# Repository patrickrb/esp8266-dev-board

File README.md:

# esp8266-dev-board
esp8266 dev board

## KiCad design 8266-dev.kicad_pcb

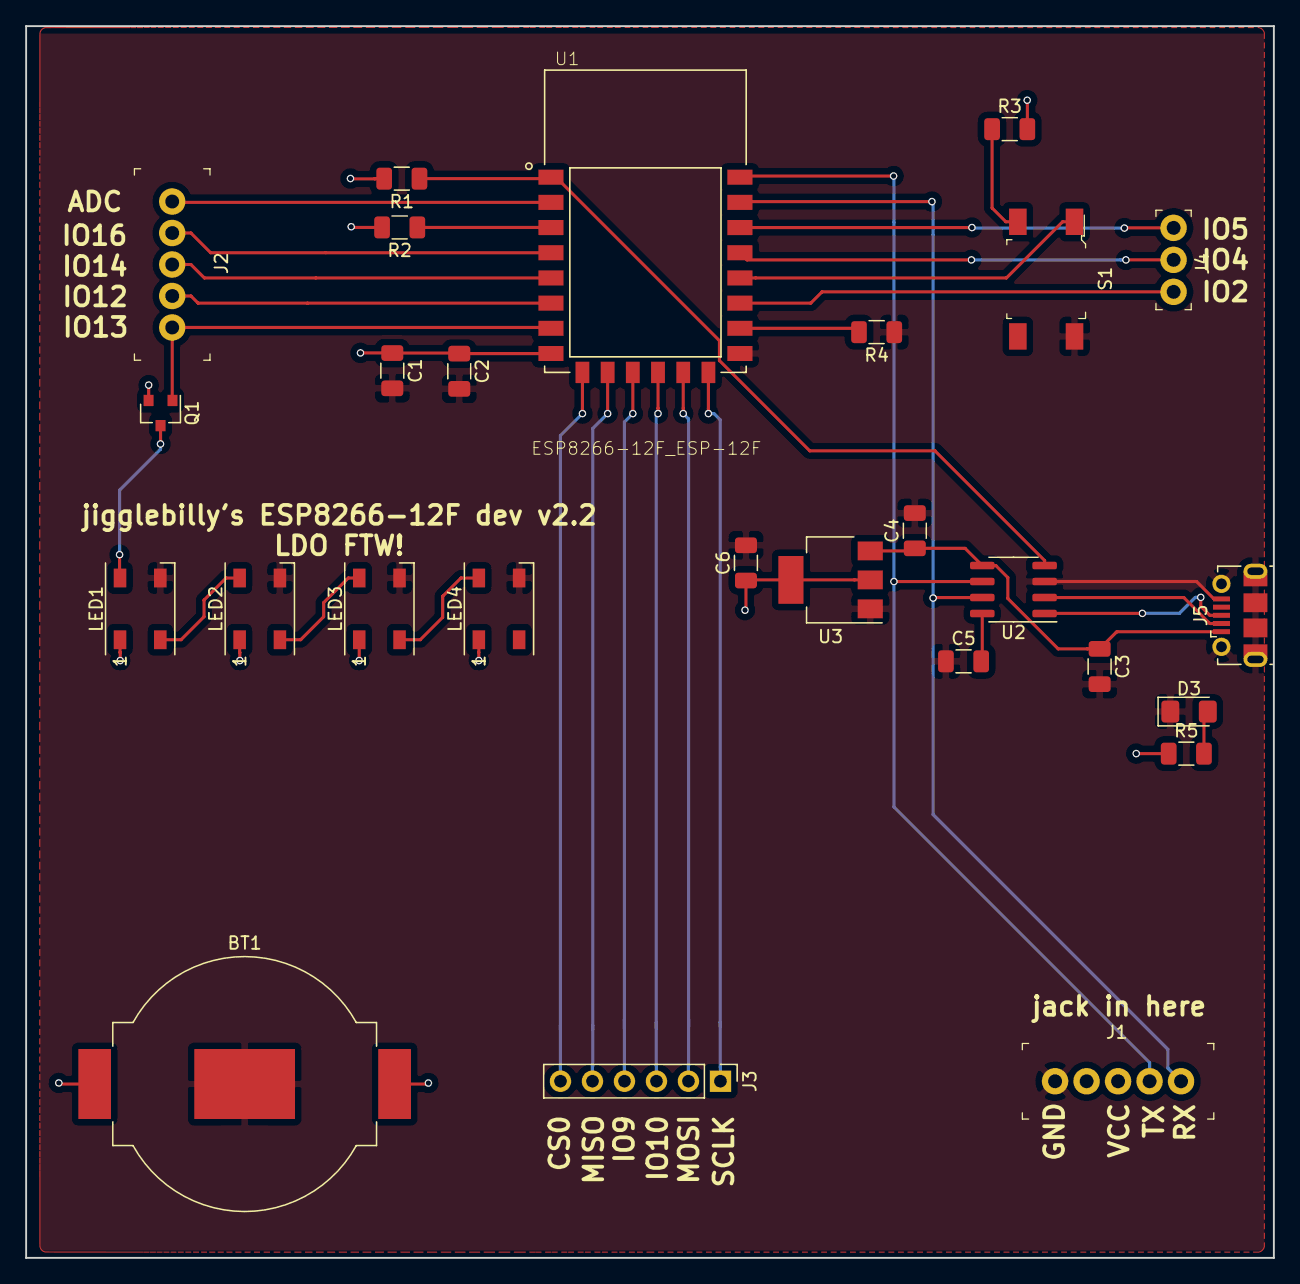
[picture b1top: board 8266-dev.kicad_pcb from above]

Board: 2 copper layers, 99.1 x 97.8 mm, 27 parts (0 on the bottom side), 32 nets.

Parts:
BT1: Battery; BatteryHolder_MPD_BC2003_1x2032
C1: 10uF; C_1206_3216Metric
C2, C3, C5: 100nF; C_1206_3216Metric
C4, C6: 1uF; C_1206_3216Metric
D3: GREEN LED; LED_1206_3216Metric_Pad1.42x1.75mm_HandSolder
J1: Programming headers; PinHeader_1x5_P2.5mm_Drill1.1mm
J2: Left breakout; PinHeader_1x5_P2.5mm_Drill1.1mm
J3: Bottom breakout; PinHeader_1x06_P2.54mm_Vertical
J4: Right breakout; PinHeader_1x3_P2.54_Drill1.1mm
J5: USB_B_Micro; USB_Micro-B_Molex-105017-0001
LED1, LED2, LED3, LED4: WS2812B; LED_WS2812B_PLCC4_5.0x5.0mm_P3.2mm
Q1: BSS138; SOT-23
R1, R2, R3, R4: 10K; R_1206_3216Metric
R5: R; R_1206_3216Metric
S1: 430152070826; Switch_Tactile_SMD_6x6mm
U1: ESP8266-12F_ESP-12F; XCVR_ESP8266-12E%2fESP-12E
U2: CH330N; SOIC-8_3.9x4.9mm_P1.27mm
U3: TLV1117-33; SOT-223-3_TabPin2

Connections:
/ADC: J2.1, U1.2
/CS0: J3.6, U1.9
/D+: J5.3, U2.1
/D-: J5.2, U2.2
/IO2: J4.3, U1.17
/IO4: J4.2, U1.19
/IO5: J4.1, U1.20
/IO9: J3.4, U1.11
/IO10: J3.3, U1.12
/IO12: J2.4, U1.6
/IO13: J2.5, Q1.1, U1.7
/IO14: J2.3, U1.5
/IO16: J2.2, U1.4
/MISO: J3.5, U1.10
/MOSI: J3.2, U1.13
/RTS: R1.1, U1.1, U2.4
/SCLK: J3.1, U1.14
/VBUS: C3.1, C4.1, J5.1, U2.5, U3.3
/VCC: BT1.1, C1.1, C2.1, C6.1, J1.3, LED1.1, LED2.1, LED3.1, LED4.1, Q1.2, R1.2, R2.2, R3.2, R5.1, U1.8, U3.2
/rx: J1.5, U1.21, U2.7
/tx: J1.4, U1.22, U2.6
GND: BT1.2, C1.2, C2.2, C3.2, C4.2, C5.1, C6.2, D3.1, J1.1, J5.5, J5.6, LED1.3, LED2.3, LED3.3, LED4.3, R4.1, S1.2, U1.15, U2.3, U3.1
unnamed: C5.2, U2.8
unnamed: D3.2, R5.2
unnamed: LED1.2, LED2.4
unnamed: LED1.4, Q1.3
unnamed: LED2.2, LED3.4
unnamed: LED3.2, LED4.4
unnamed: R2.1, U1.3
unnamed: R3.1, S1.3
unnamed: R4.2, U1.16
unnamed: S1.1, U1.18

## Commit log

2019-05-21 first commit, working on FTDI
2019-07-17 updated to v1
2019-07-18 added logic level shifter and some WS2812B's
2019-08-28 added power light, CH330N, and some neopixels
2020-01-24 added LDO and re-swapped the tx/rx lines, removed one cap
2020-01-24 latest version
